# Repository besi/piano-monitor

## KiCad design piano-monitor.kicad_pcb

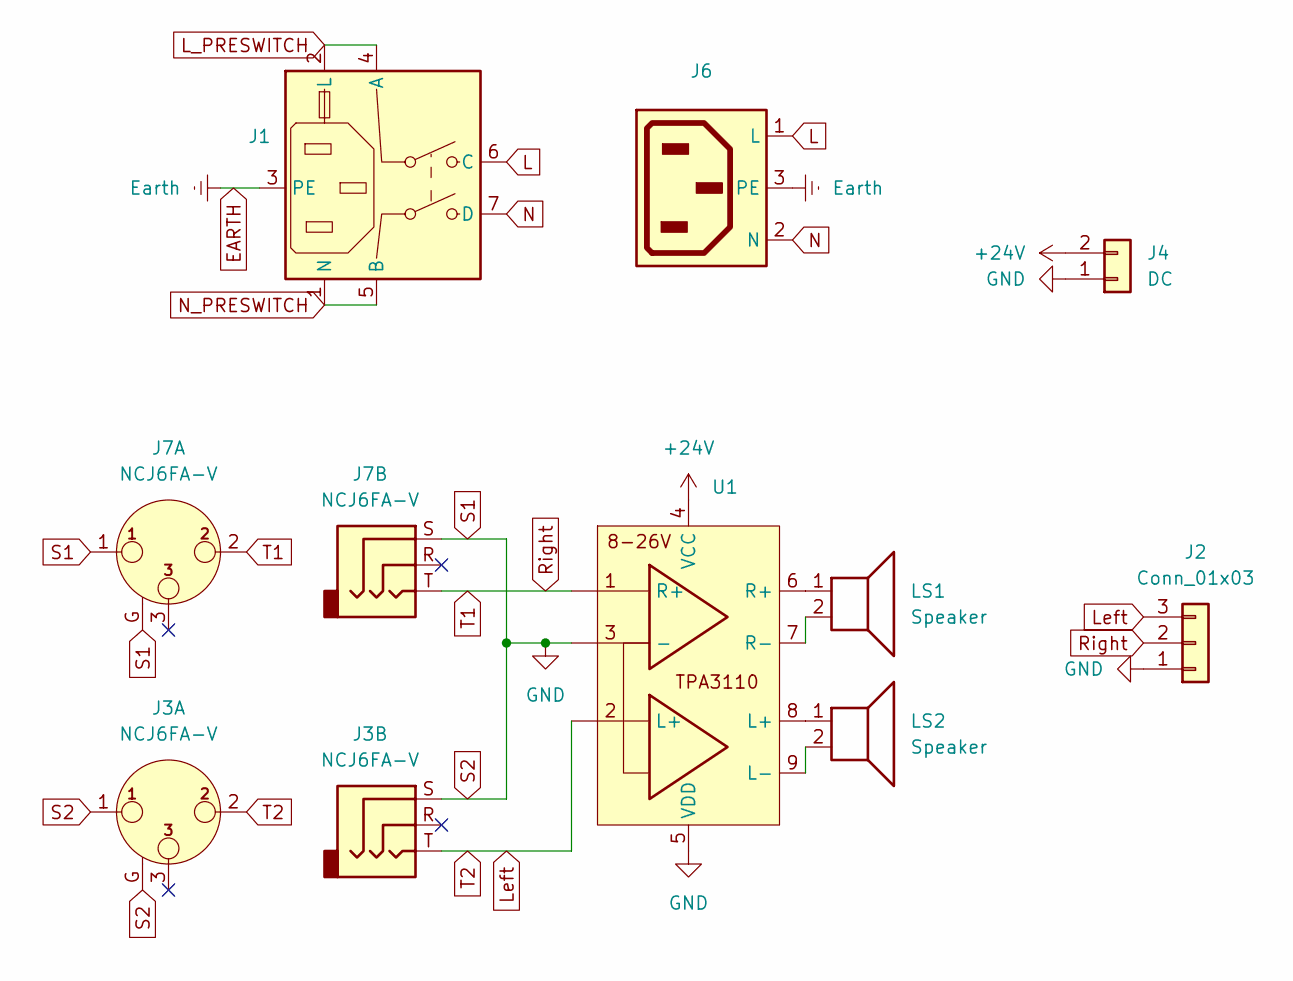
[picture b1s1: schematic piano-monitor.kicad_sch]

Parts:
J1: iec320-c14
J2: Conn_01x03; PinHeader_1x03_P2.54mm_Vertical
J3, J7: NCJ6FA-V; Jack_XLR-6.35mm_Neutrik_NCJ6FA-V_Vertical
J4: DC; PinHeader_1x02_P2.54mm_Vertical
J6: c14-outlet
LS1, LS2: Speaker; PinHeader_1x02_P2.54mm_Vertical
U1: tpa3110

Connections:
+24V: J4.2, U1.4 (VCC)
EARTH: J1.3 (PE), J6.3 (PE)
L: J1.6 (C), J6.1 (L)
L_PRESWITCH: J1.2 (L), J1.4 (A)
Left: J2.3, J3.2, J3.T, U1.2 (L+)
N: J1.7 (D), J6.2 (N)
N_PRESWITCH: J1.1 (N), J1.5 (B)
unnamed: LS1.1, U1.6 (R+)
unnamed: LS2.1, U1.8 (L+)
unnamed: LS2.2, U1.9 (L-)
unnamed: LS1.2, U1.7 (R-)
Right: J2.2, J7.2, J7.T, U1.1 (R+)
S1: J2.1, J3.1, J3.G, J3.S, J4.1, J7.1, J7.G, J7.S, U1.3 (-), U1.5 (VDD)

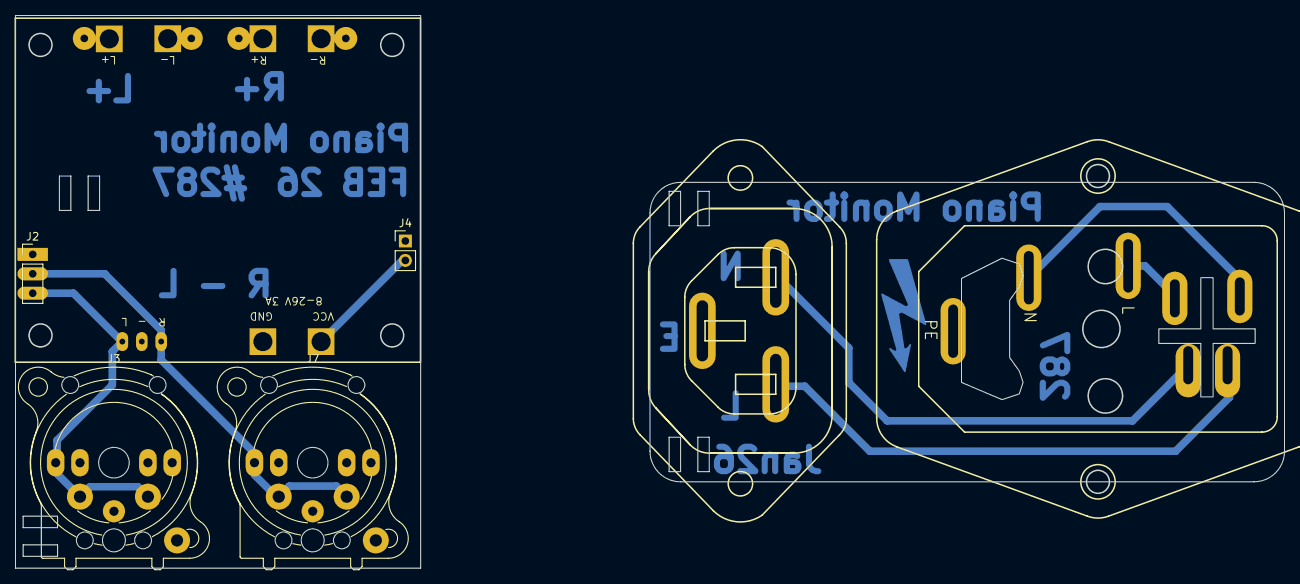
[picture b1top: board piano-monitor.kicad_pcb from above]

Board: 2 copper layers, 165.8 x 72.2 mm, 9 parts (0 on the bottom side), 13 nets.

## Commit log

2026-01-28 Initial commit with C14 power inlet
2026-01-28 Add tpa3110 footprint
2026-01-28 Add gitignore
2026-01-28 Add initial schematic
2026-01-29 Update the C14 plug symbol and footprint
2026-01-29 Update PCB
2026-01-29 Update Schematic
2026-01-29 Add some traces
2026-01-30 Update TPA3110
2026-01-30 Update schematic and prepare for the AC pcb to be milled out with a 0.8mm bit
2026-01-30 prepare for plot
2026-01-30 Update AC footprints
2026-01-30 Update measurements of C14 footprint
2026-02-17 Update submodules
2026-02-17 Ignore fab folder
2026-02-18 Finalise the AMP pcb
2026-02-18 Fill zones
2026-03-30 Add holder for 28mm dowel
